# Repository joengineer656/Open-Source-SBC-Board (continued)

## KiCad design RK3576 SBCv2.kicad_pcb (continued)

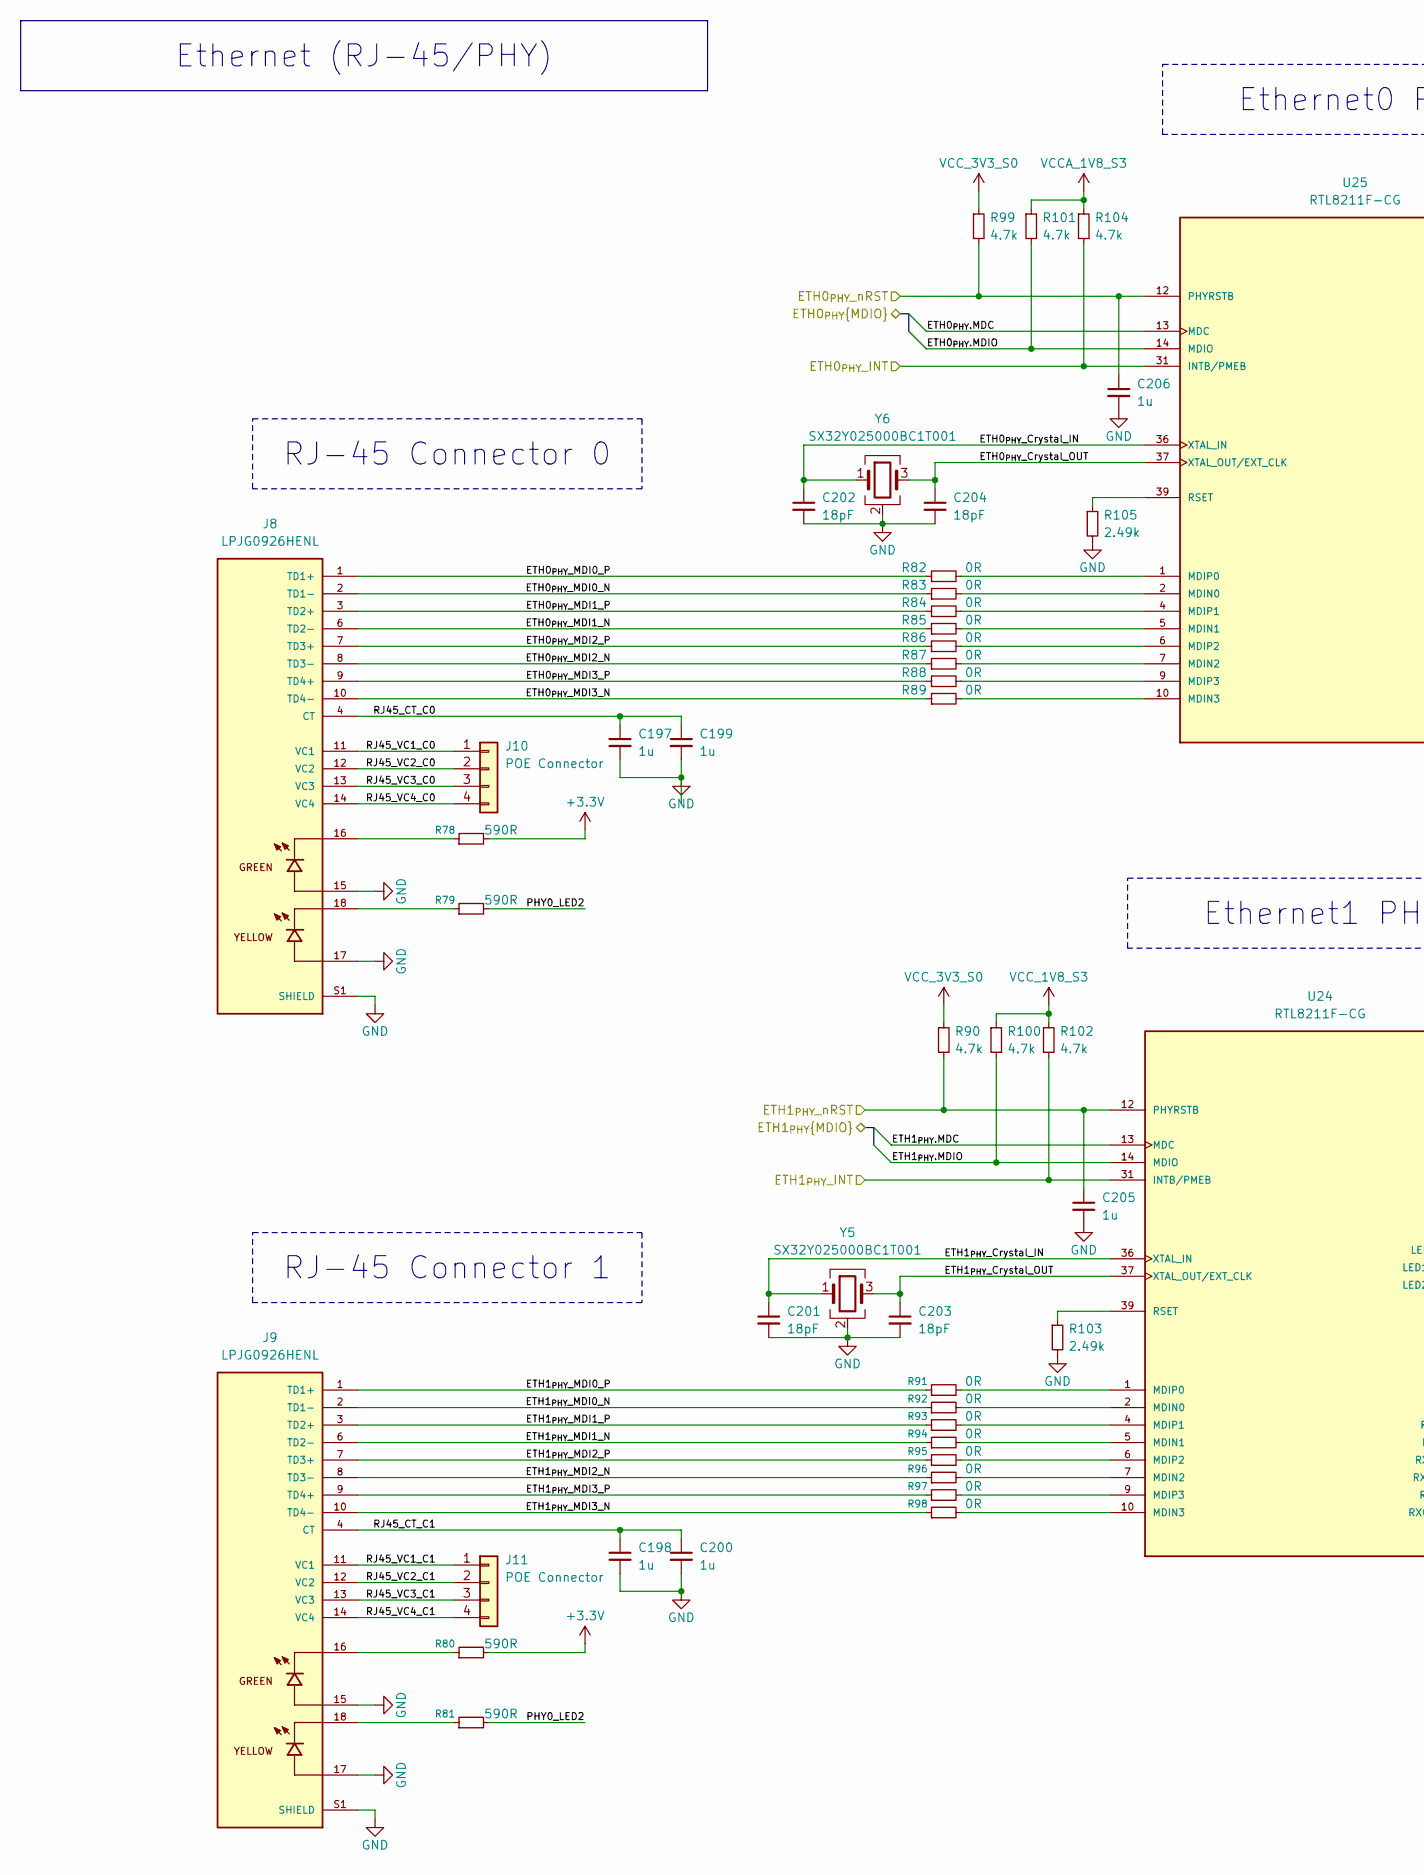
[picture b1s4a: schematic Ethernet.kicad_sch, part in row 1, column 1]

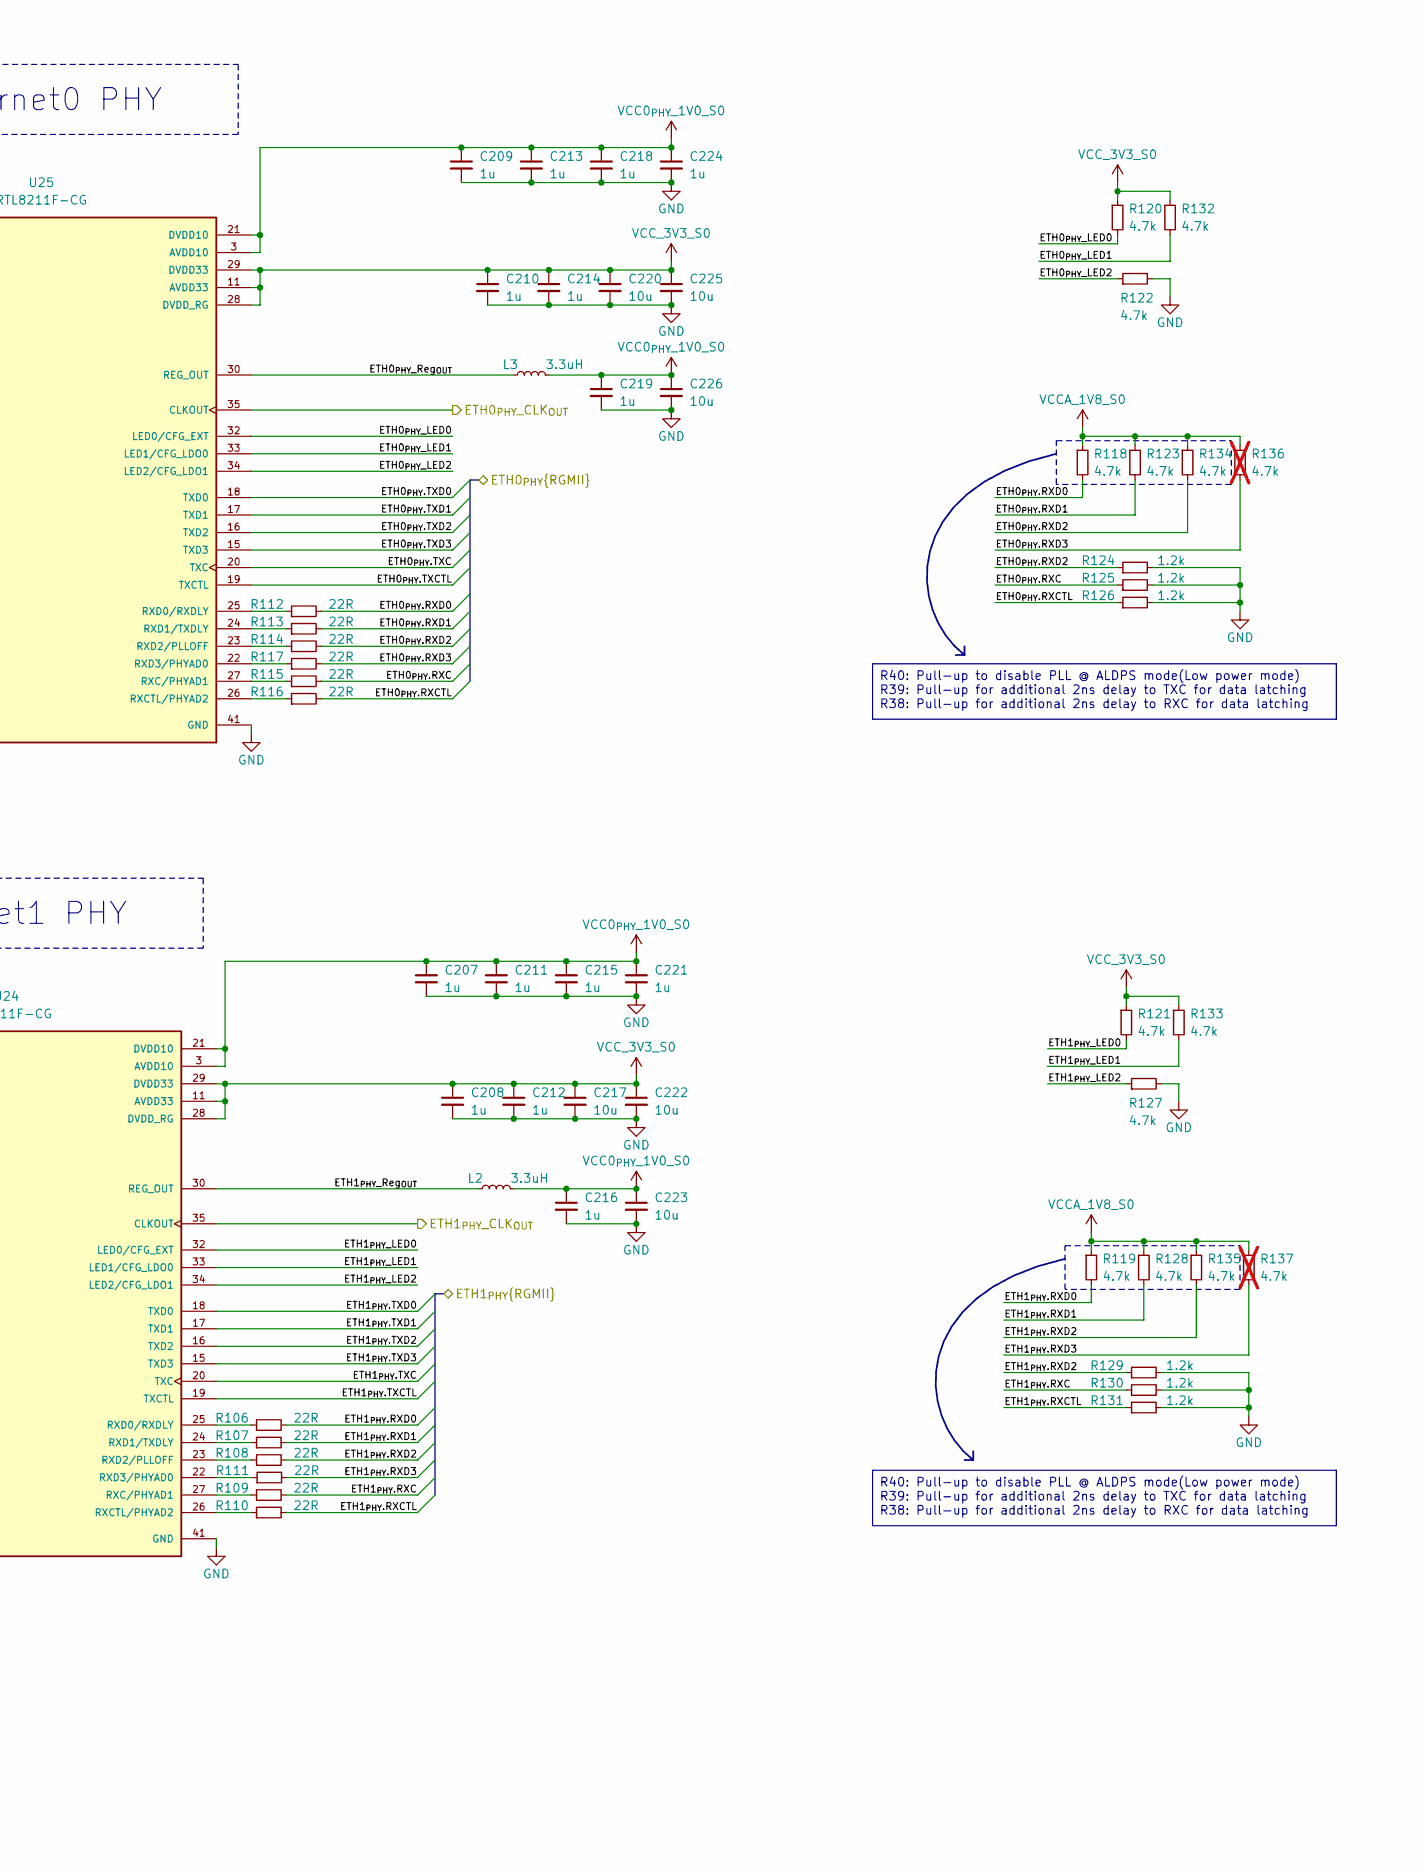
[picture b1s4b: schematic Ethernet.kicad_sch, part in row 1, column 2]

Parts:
C197, C198, C199, C200, C205, C206, C207, C208, C209, C210, C211, C212, C213, C214, C215, C216, C218, C219, C221, C224: 1u; C_0201_0603Metric_Pad0.64x0.40mm_HandSolder; Mouser Part CL03A105KP3NSNC; LCSC Part C5209398
C201, C202, C203, C204: 18pF; C_0402_1005Metric; Mouser Part 603-CC402FRNPO9BN180; LCSC Part C541431
C217, C220, C222, C223, C225, C226: 10u; C_0603_1608Metric; Mouser Part 187-CL10A106KP8NNNC; LCSC Part C19702
J8, J9: LPJG0926HENL; PARTREV A; LCSC Part C22457393
J10, J11: POE Connector; PinHeader_2x02_P2.54mm_Vertical; Mouser Part 200-TSW10207GDLL001; LCSC Part C66690
L2, L3: 3.3uH; L_Coilcraft_0805HQ_2012Metric; LCSC Part C2926398
R78, R79, R80, R81: 590R; R_0402_1005Metric; Mouser Part 603-RC0402FR-07590RL; LCSC Part C327335
R82, R83, R84, R85, R86, R87, R88, R89, R91, R92, R93, R94, R95, R96, R97, R98: 0R; R_0402_1005Metric; Mouser Part 603-RC0402FR-070RL; LCSC Part C106231
R90, R99, R100, R101, R102, R104, R118, R119, R120, R121, R122, R123, R127, R128, R132, R133, R134, R135: 4.7k; R_0402_1005Metric; Mouser Part 603-RC0402FR-074K7L; LCSC Part C105871
R103, R105: 2.49k; R_0402_1005Metric; Mouser Part 603-RC0402FR-074K7L; LCSC Part C105871
R106, R107, R108, R109, R110, R111, R112, R113, R114, R115, R116, R117: 22R; R_0402_1005Metric; Mouser Part 603-RC0402FR-070RL; LCSC Part C106231
R124, R125, R126, R129, R130, R131: 1.2k; R_0402_1005Metric; Mouser Part 603-RC0402FR-071K2L; LCSC Part C138040
R136, R137: 4.7k; R_0402_1005Metric; Mouser Part 603-RC0402FR-074K7L; LCSC Part C105871; not fitted
U24, U25: RTL8211F-CG; RTL8211F-CG_QFN-40-1EP_5x5mm_P0.4mm; PARTREV 1.4; LCSC Part C187932
Y5, Y6: SX32Y025000BC1T001; Crystal_SMD_3225-4Pin_3.2x2.5mm_HandSoldering; LCSC Part C20612981

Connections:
/Ethernet/ETH0_{PHY}.MDC: U25.13 (MDC); also elsewhere on the board
/Ethernet/ETH0_{PHY}.MDIO: R101.2, U25.14 (MDIO); also elsewhere on the board
/Ethernet/ETH0_{PHY}.RXC: R115.2, R125.1; also elsewhere on the board
/Ethernet/ETH0_{PHY}.RXCTL: R116.2, R126.1; also elsewhere on the board
/Ethernet/ETH0_{PHY}.RXD0: R112.2, R118.2; also elsewhere on the board
/Ethernet/ETH0_{PHY}.RXD1: R113.2, R123.2; also elsewhere on the board
/Ethernet/ETH0_{PHY}.RXD2: R114.2, R124.1, R134.2; also elsewhere on the board
/Ethernet/ETH0_{PHY}.RXD3: R117.2, R136.2; also elsewhere on the board
/Ethernet/ETH0_{PHY}.TXC: U25.20 (TXC); also elsewhere on the board
/Ethernet/ETH0_{PHY}.TXCTL: U25.19 (TXCTL); also elsewhere on the board
/Ethernet/ETH0_{PHY}.TXD0: U25.18 (TXD0); also elsewhere on the board
/Ethernet/ETH0_{PHY}.TXD1: U25.17 (TXD1); also elsewhere on the board
/Ethernet/ETH0_{PHY}.TXD2: U25.16 (TXD2); also elsewhere on the board
/Ethernet/ETH0_{PHY}.TXD3: U25.15 (TXD3); also elsewhere on the board
/Ethernet/ETH0_{PHY}_CLK_{OUT}: U25.35 (CLKOUT); also elsewhere on the board
/Ethernet/ETH0_{PHY}_Crystal_IN: C202.1, U25.36 (XTAL_IN), Y6.1
/Ethernet/ETH0_{PHY}_Crystal_OUT: C204.1, U25.37 (XTAL_OUT/EXT_CLK), Y6.3
/Ethernet/ETH0_{PHY}_INT: R104.2, U25.31 (INTB/PMEB); also elsewhere on the board
/Ethernet/ETH0_{PHY}_LED0: R120.2, U25.32 (LED0/CFG_EXT)
/Ethernet/ETH0_{PHY}_LED1: R132.2, U25.33 (LED1/CFG_LDO0)
/Ethernet/ETH0_{PHY}_LED2: R122.1, U25.34 (LED2/CFG_LDO1)
/Ethernet/ETH0_{PHY}_MDI0_N: J8.2 (TD1-), R83.1
/Ethernet/ETH0_{PHY}_MDI0_P: J8.1 (TD1+), R82.1
/Ethernet/ETH0_{PHY}_MDI1_N: J8.6 (TD2-), R85.1
/Ethernet/ETH0_{PHY}_MDI1_P: J8.3 (TD2+), R84.1
/Ethernet/ETH0_{PHY}_MDI2_N: J8.8 (TD3-), R87.1
/Ethernet/ETH0_{PHY}_MDI2_P: J8.7 (TD3+), R86.1
/Ethernet/ETH0_{PHY}_MDI3_N: J8.10 (TD4-), R89.1
/Ethernet/ETH0_{PHY}_MDI3_P: J8.9 (TD4+), R88.1
/Ethernet/ETH0_{PHY}_Reg_{OUT}: L3.1, U25.30 (REG_OUT)
/Ethernet/ETH0_{PHY}_nRST: C206.1, R99.2, U25.12 (PHYRSTB); also elsewhere on the board
/Ethernet/ETH1_{PHY}.MDC: U24.13 (MDC); also elsewhere on the board
/Ethernet/ETH1_{PHY}.MDIO: R100.2, U24.14 (MDIO); also elsewhere on the board
/Ethernet/ETH1_{PHY}.RXC: R109.2, R130.1; also elsewhere on the board
/Ethernet/ETH1_{PHY}.RXCTL: R110.2, R131.1; also elsewhere on the board
/Ethernet/ETH1_{PHY}.RXD0: R106.2, R119.2; also elsewhere on the board
/Ethernet/ETH1_{PHY}.RXD1: R107.2, R128.2; also elsewhere on the board
/Ethernet/ETH1_{PHY}.RXD2: R108.2, R129.1, R135.2; also elsewhere on the board
/Ethernet/ETH1_{PHY}.RXD3: R111.2, R137.2; also elsewhere on the board
/Ethernet/ETH1_{PHY}.TXC: U24.20 (TXC); also elsewhere on the board
/Ethernet/ETH1_{PHY}.TXCTL: U24.19 (TXCTL); also elsewhere on the board
/Ethernet/ETH1_{PHY}.TXD0: U24.18 (TXD0); also elsewhere on the board
/Ethernet/ETH1_{PHY}.TXD1: U24.17 (TXD1); also elsewhere on the board
/Ethernet/ETH1_{PHY}.TXD2: U24.16 (TXD2); also elsewhere on the board
/Ethernet/ETH1_{PHY}.TXD3: U24.15 (TXD3); also elsewhere on the board
/Ethernet/ETH1_{PHY}_CLK_{OUT}: U24.35 (CLKOUT); also elsewhere on the board
/Ethernet/ETH1_{PHY}_Crystal_IN: C201.1, U24.36 (XTAL_IN), Y5.1
/Ethernet/ETH1_{PHY}_Crystal_OUT: C203.1, U24.37 (XTAL_OUT/EXT_CLK), Y5.3
/Ethernet/ETH1_{PHY}_INT: R102.2, U24.31 (INTB/PMEB); also elsewhere on the board
/Ethernet/ETH1_{PHY}_LED0: R121.2, U24.32 (LED0/CFG_EXT)
/Ethernet/ETH1_{PHY}_LED1: R133.2, U24.33 (LED1/CFG_LDO0)
/Ethernet/ETH1_{PHY}_LED2: R127.1, U24.34 (LED2/CFG_LDO1)
/Ethernet/ETH1_{PHY}_MDI0_N: J9.2 (TD1-), R92.1
/Ethernet/ETH1_{PHY}_MDI0_P: J9.1 (TD1+), R91.1
/Ethernet/ETH1_{PHY}_MDI1_N: J9.6 (TD2-), R94.1
/Ethernet/ETH1_{PHY}_MDI1_P: J9.3 (TD2+), R93.1
/Ethernet/ETH1_{PHY}_MDI2_N: J9.8 (TD3-), R96.1
/Ethernet/ETH1_{PHY}_MDI2_P: J9.7 (TD3+), R95.1
/Ethernet/ETH1_{PHY}_MDI3_N: J9.10 (TD4-), R98.1
/Ethernet/ETH1_{PHY}_MDI3_P: J9.9 (TD4+), R97.1
/Ethernet/ETH1_{PHY}_Reg_{OUT}: L2.1, U24.30 (REG_OUT)
/Ethernet/ETH1_{PHY}_nRST: C205.1, R90.2, U24.12 (PHYRSTB); also elsewhere on the board
/Ethernet/PHY0_LED2: R79.2, R81.2
/Ethernet/RJ45_CT_C0: C197.1, C199.1, J8.4 (CT), J8.5 (CT)
/Ethernet/RJ45_CT_C1: C198.1, C200.1, J9.4 (CT), J9.5 (CT)
/Ethernet/RJ45_VC1_C0: J8.11 (VC1), J10.1
/Ethernet/RJ45_VC1_C1: J9.11 (VC1), J11.1
/Ethernet/RJ45_VC2_C0: J8.12 (VC2), J10.2
/Ethernet/RJ45_VC2_C1: J9.12 (VC2), J11.2
/Ethernet/RJ45_VC3_C0: J8.13 (VC3), J10.3
/Ethernet/RJ45_VC3_C1: J9.13 (VC3), J11.3
/Ethernet/RJ45_VC4_C0: J8.14 (VC4), J10.4
/Ethernet/RJ45_VC4_C1: J9.14 (VC4), J11.4
unnamed: J8.16, R78.1
unnamed: J8.18, R79.1
unnamed: J9.16, R80.1
unnamed: J9.18, R81.1
unnamed: R92.2, U24.2 (MDIN0)
unnamed: R94.2, U24.5 (MDIN1)
unnamed: R96.2, U24.7 (MDIN2)
unnamed: R98.2, U24.10 (MDIN3)
unnamed: R91.2, U24.1 (MDIP0)
unnamed: R93.2, U24.4 (MDIP1)
unnamed: R95.2, U24.6 (MDIP2)
unnamed: R97.2, U24.9 (MDIP3)
unnamed: R103.1, U24.39 (RSET)
unnamed: R110.1, U24.26 (RXCTL/PHYAD2)
unnamed: R109.1, U24.27 (RXC/PHYAD1)
unnamed: R106.1, U24.25 (RXD0/RXDLY)
unnamed: R107.1, U24.24 (RXD1/TXDLY)
unnamed: R108.1, U24.23 (RXD2/PLLOFF)
unnamed: R111.1, U24.22 (RXD3/PHYAD0)
unnamed: R83.2, U25.2 (MDIN0)
unnamed: R85.2, U25.5 (MDIN1)
unnamed: R87.2, U25.7 (MDIN2)
unnamed: R89.2, U25.10 (MDIN3)
unnamed: R82.2, U25.1 (MDIP0)
unnamed: R84.2, U25.4 (MDIP1)
unnamed: R86.2, U25.6 (MDIP2)
unnamed: R88.2, U25.9 (MDIP3)
unnamed: R105.1, U25.39 (RSET)
unnamed: R116.1, U25.26 (RXCTL/PHYAD2)
unnamed: R115.1, U25.27 (RXC/PHYAD1)
unnamed: R112.1, U25.25 (RXD0/RXDLY)
unnamed: R113.1, U25.24 (RXD1/TXDLY)
unnamed: R114.1, U25.23 (RXD2/PLLOFF)
unnamed: R117.1, U25.22 (RXD3/PHYAD0)
VCC0_{PHY}_1V0_S0: C207.1, C209.1, C211.1, C213.1, C215.1, C216.1, C218.1, C219.1, C221.1, C223.1, C224.1, C226.1, L2.2, L3.2, U24.3 (AVDD10), U24.8 (AVDD10), U24.21 (DVDD10), U24.38 (AVDD10), U25.3 (AVDD10), U25.8 (AVDD10), U25.21 (DVDD10), U25.38 (AVDD10)
VCCA_1V8_S3: R101.1, R104.1; also elsewhere on the board

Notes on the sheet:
R40: Pull-up to disable PLL @ ALDPS mode(Low power mode) R39: Pull-up for additional 2ns delay to TXC for data latching R38: Pull-up for additional 2ns delay to RXC for data latching
RJ-45 Connector 1
Ethernet (RJ-45/PHY)
Ethernet1 PHY
Ethernet0 PHY
RJ-45 Connector 0

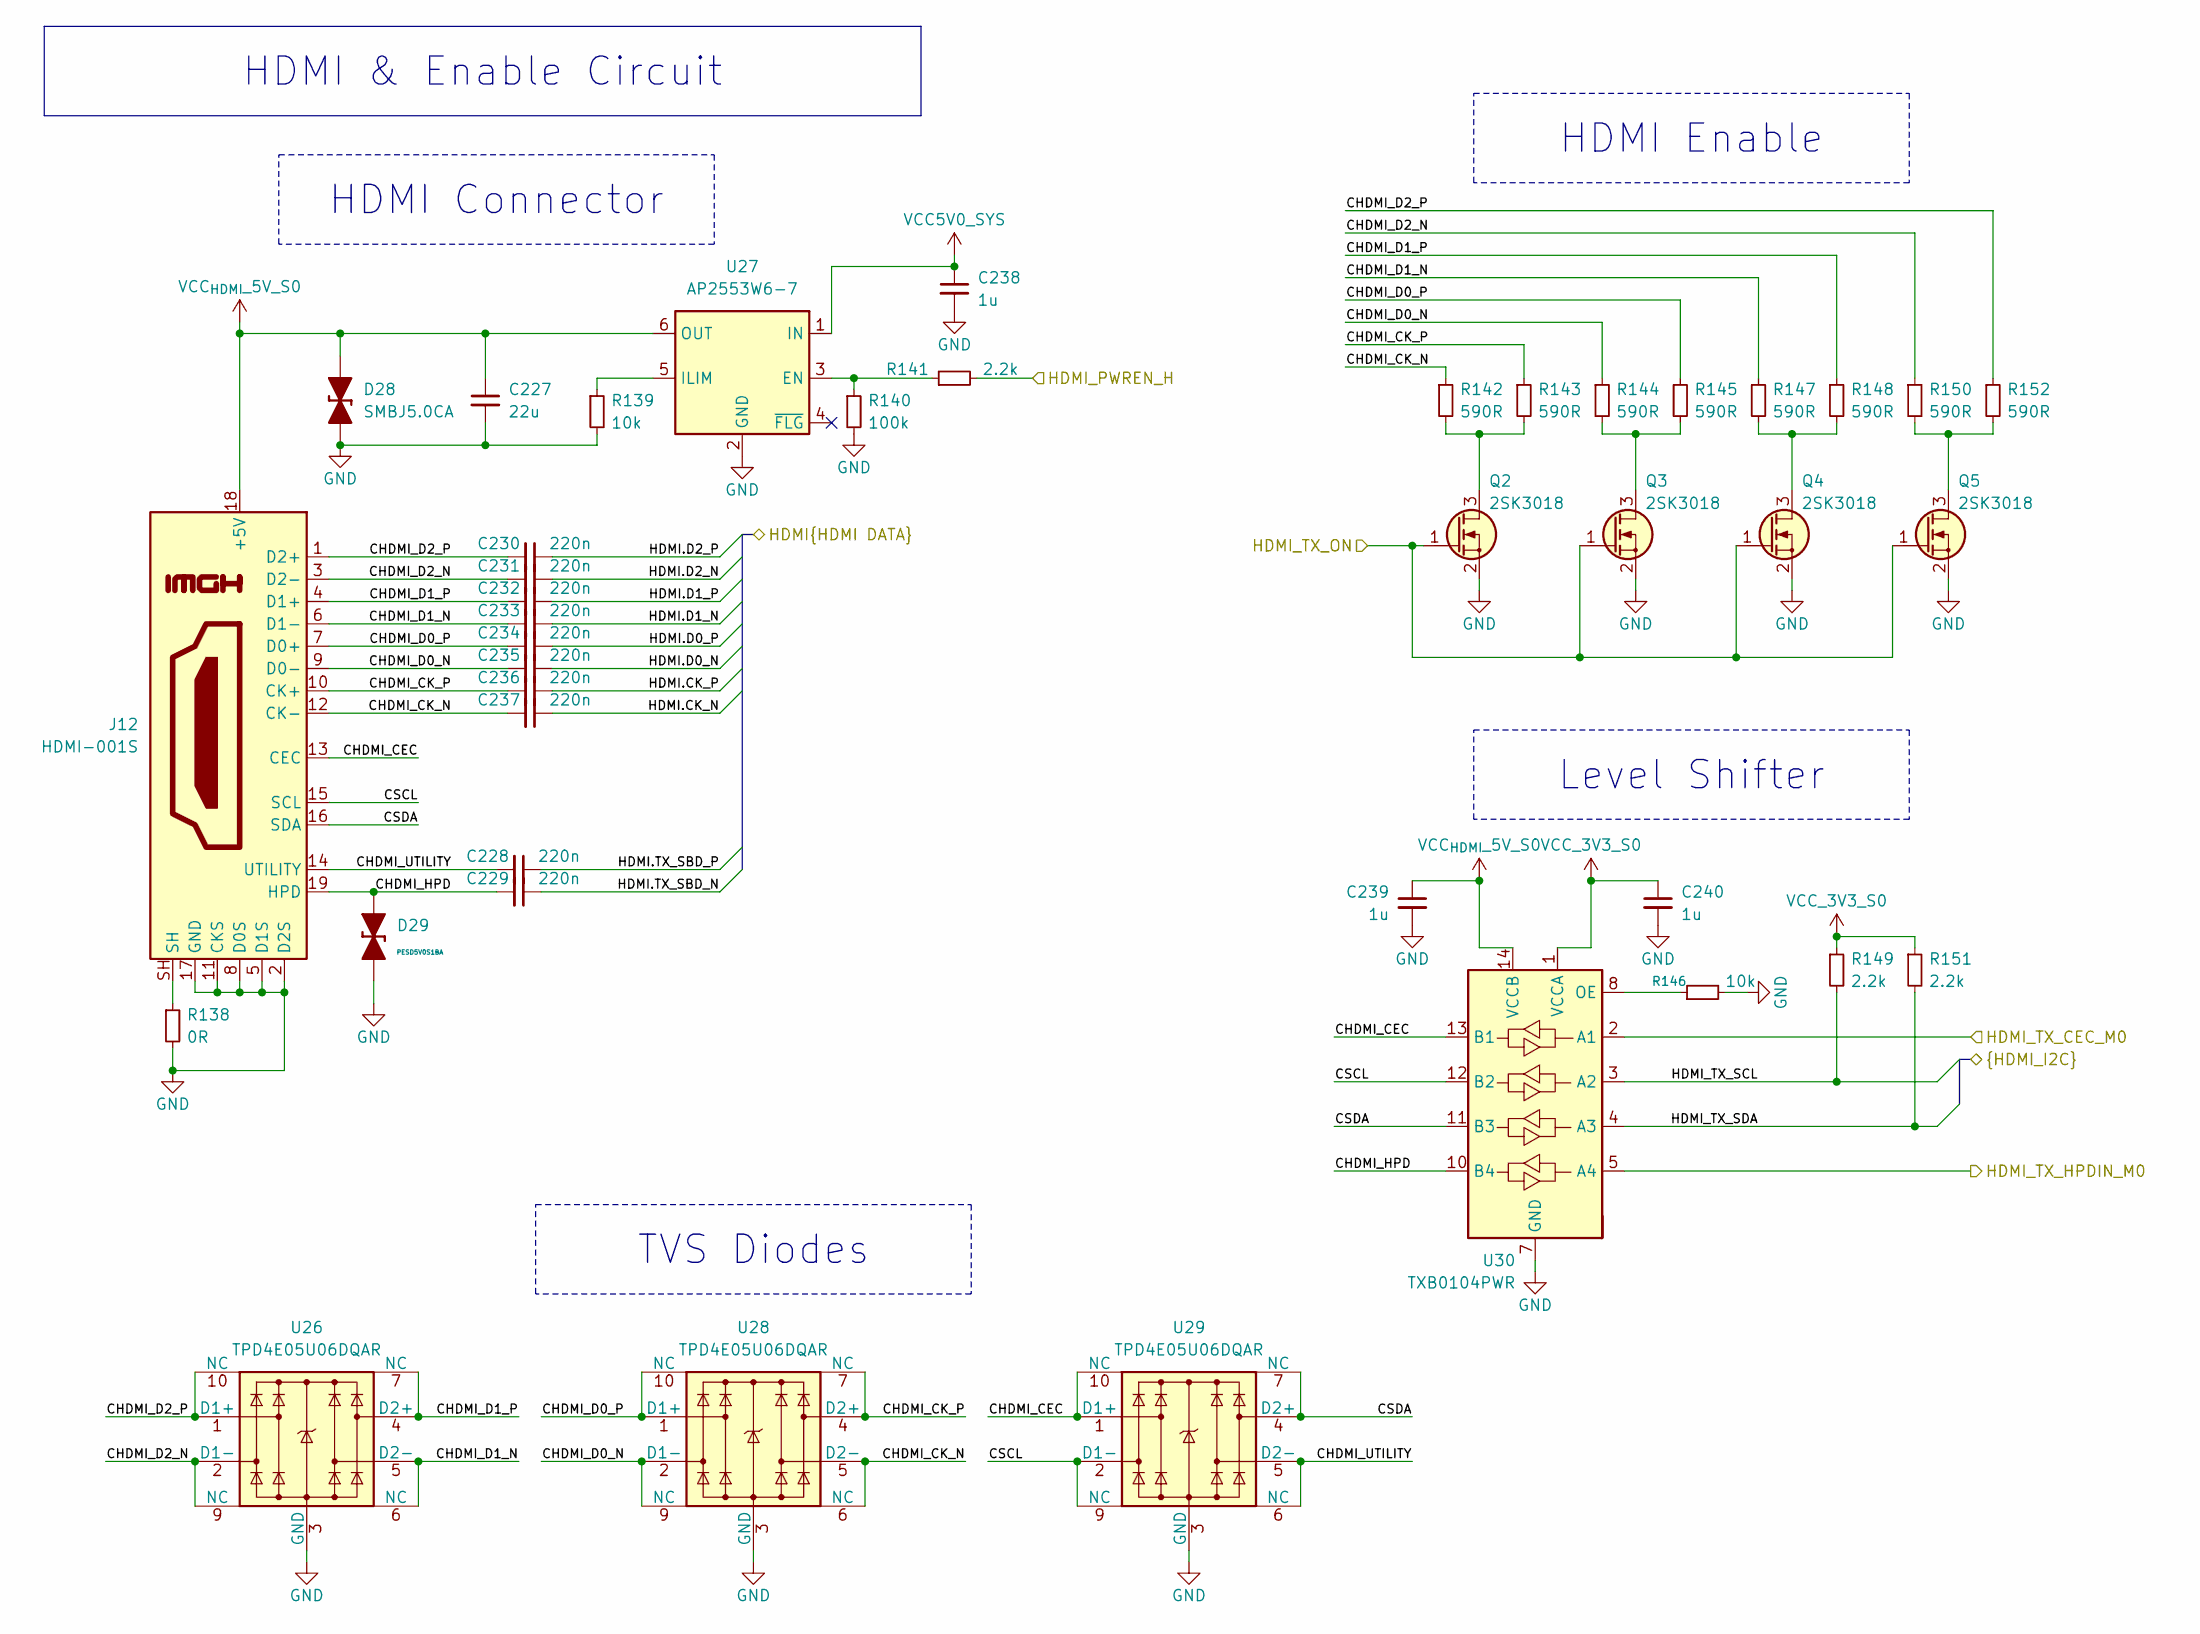
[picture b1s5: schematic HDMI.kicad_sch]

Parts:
C227: 22u; C_0603_1608Metric; Mouser Part CL10A226MP8NUNE; LCSC Part C86295
C228, C229, C230, C231, C232, C233, C234, C235, C236, C237: 220n; C_0201_0603Metric_Pad0.64x0.40mm_HandSolder; Mouser Part 603-CC0201KRX56BB224; LCSC Part C326658
C238, C239, C240: 1u; C_0201_0603Metric_Pad0.64x0.40mm_HandSolder; Mouser Part CL03A105KP3NSNC; LCSC Part C5209398
D28: SMBJ5.0CA; D_SMB_TVS; Mouser Part 581-SMBJ5.0CA; LCSC Part C113975
D29: PESD5V0S1BA; D_SOD-323_TVS; Mouser Part 771-PESD5V0S1BA-T/R; LCSC Part C5158048
J12: HDMI-001S; HDMI_A_Amphenol_10029449-x01xLF_Horizontal; LCSC Part C720616
Q2, Q3, Q4, Q5: 2SK3018; SOT-323_SC-70; LCSC Part C20069148
R138: 0R; R_0402_1005Metric; Mouser Part 603-RC0402FR-070RL; LCSC Part C106231
R139, R146: 10k; R_0402_1005Metric; Mouser Part 603-RC0402FR-0710KL; LCSC Part C60490
R140: 100k; R_0402_1005Metric; Mouser Part 603-RC0402FR-0710KL; LCSC Part C60490
R141, R149, R151: 2.2k; R_0402_1005Metric; Mouser Part 603-RC0402FR-072K2L; LCSC Part C114762
R142, R143, R144, R145, R147, R148, R150, R152: 590R; R_0402_1005Metric; Mouser Part 603-RC0402FR-07590RL; LCSC Part C327335
U26, U28, U29: TPD4E05U06DQAR; USON-10_2.5x1.0mm_P0.5mm; Mouser Part 595-TPD4E05U06DQAR; LCSC Part C138714
U27: AP2553W6-7; SOT-23-6_Handsoldering; Mouser Part 621-AP2553W6-7; LCSC Part C212302
U30: TXB0104PWR; TSSOP-14_4.4x5mm_P0.65mm; Mouser Part 595-TXB0104PWR; LCSC Part C60708

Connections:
/HDMI/CHDMI_CEC: J12.13 (CEC), U29.1 (D1+), U29.10 (NC), U30.13 (B1)
/HDMI/CHDMI_CK_N: C237.2, J12.12 (CK-), R142.1, U28.5 (D2-), U28.6 (NC)
/HDMI/CHDMI_CK_P: C236.2, J12.10 (CK+), R143.1, U28.4 (D2+), U28.7 (NC)
/HDMI/CHDMI_D0_N: C235.2, J12.9 (D0-), R144.1, U28.2 (D1-), U28.9 (NC)
/HDMI/CHDMI_D0_P: C234.2, J12.7 (D0+), R145.1, U28.1 (D1+), U28.10 (NC)
/HDMI/CHDMI_D1_N: C233.2, J12.6 (D1-), R147.1, U26.5 (D2-), U26.6 (NC)
/HDMI/CHDMI_D1_P: C232.2, J12.4 (D1+), R148.1, U26.4 (D2+), U26.7 (NC)
/HDMI/CHDMI_D2_N: C231.2, J12.3 (D2-), R150.1, U26.2 (D1-), U26.9 (NC)
/HDMI/CHDMI_D2_P: C230.2, J12.1 (D2+), R152.1, U26.1 (D1+), U26.10 (NC)
/HDMI/CHDMI_HPD: C229.2, D29.2 (A), J12.19 (HPD), U30.10 (B4)
/HDMI/CHDMI_UTILITY: C228.2, J12.14 (UTILITY), U29.5 (D2-), U29.6 (NC)
/HDMI/CSCL: J12.15 (SCL), U29.2 (D1-), U29.9 (NC), U30.12 (B2)
/HDMI/CSDA: J12.16 (SDA), U29.4 (D2+), U29.7 (NC), U30.11 (B3)
/HDMI/HDMI.CK_N: C237.1
/HDMI/HDMI.CK_P: C236.1
/HDMI/HDMI.D0_N: C235.1
/HDMI/HDMI.D0_P: C234.1
/HDMI/HDMI.D1_N: C233.1
/HDMI/HDMI.D1_P: C232.1
/HDMI/HDMI.D2_N: C231.1
/HDMI/HDMI.D2_P: C230.1
/HDMI/HDMI.TX_SBD_N: C229.1
/HDMI/HDMI.TX_SBD_P: C228.1
/HDMI/HDMI_PWREN_H: R141.2; also elsewhere on the board
/HDMI/HDMI_TX_CEC_M0: U30.2 (A1); also elsewhere on the board
/HDMI/HDMI_TX_HPDIN_M0: U30.5 (A4); also elsewhere on the board
/HDMI/HDMI_TX_ON: Q2.1 (G), Q3.1 (G), Q4.1 (G), Q5.1 (G); also elsewhere on the board
/HDMI/HDMI_TX_SCL: R149.2, U30.3 (A2); also elsewhere on the board
/HDMI/HDMI_TX_SDA: R151.2, U30.4 (A3); also elsewhere on the board
unnamed: J12.SH, R138.1
unnamed: Q2.3 (D), R142.2, R143.2
unnamed: Q3.3 (D), R144.2, R145.2
unnamed: Q4.3 (D), R147.2, R148.2
unnamed: Q5.3 (D), R150.2, R152.2
unnamed: R140.1, R141.1, U27.3 (EN)
unnamed: R139.1, U27.5 (ILIM)
unnamed: R146.1, U30.8 (OE)
VCC_{HDMI}_5V_S0: C227.1, C239.1, D28.2 (A), J12.18 (+5V), U27.6 (OUT), U30.14 (VCCB)

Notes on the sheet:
TVS Diodes
HDMI Connector
Level Shifter
HDMI & Enable Circuit
HDMI Enable

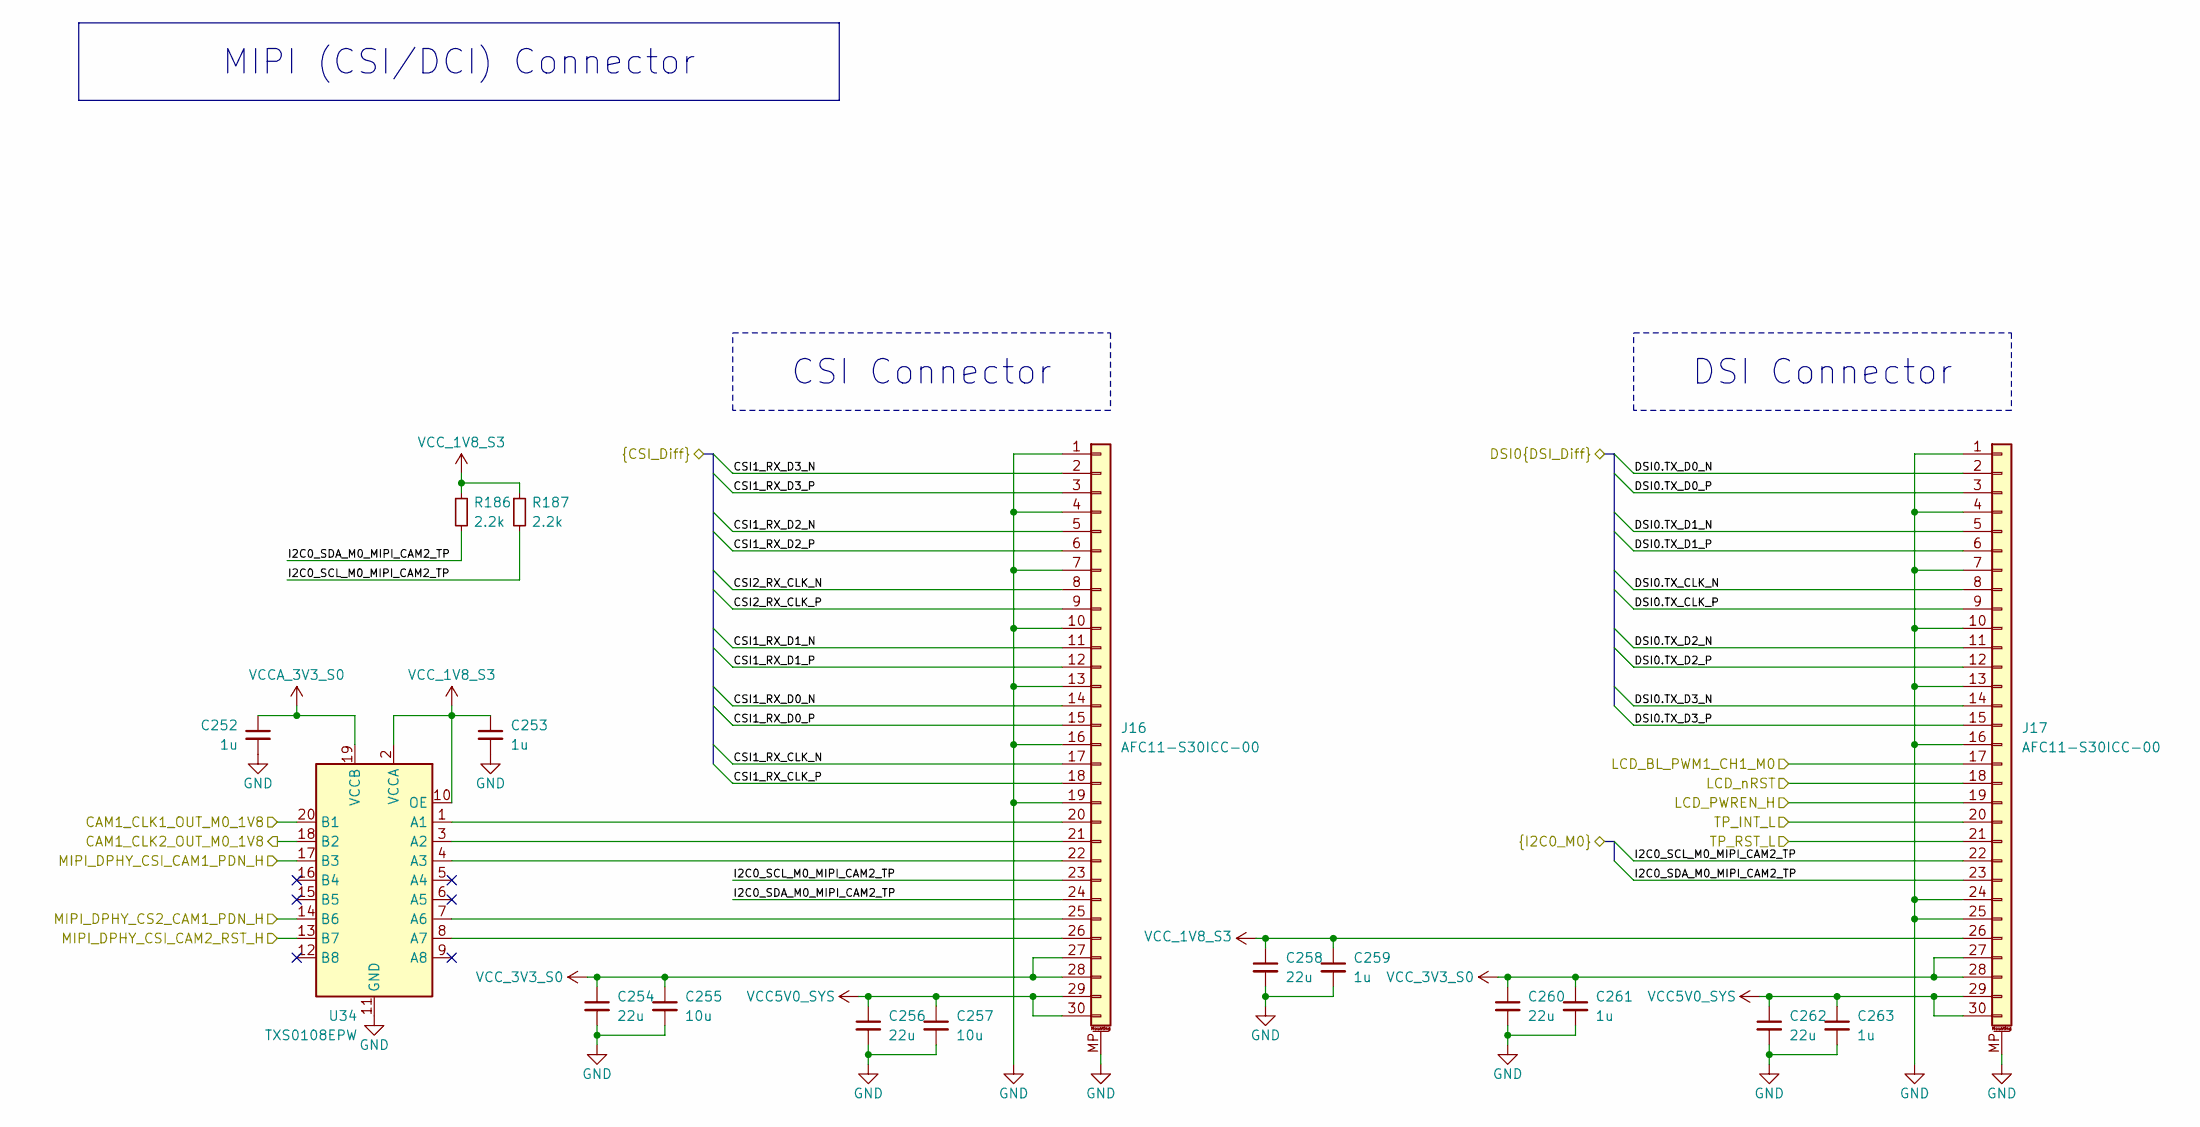
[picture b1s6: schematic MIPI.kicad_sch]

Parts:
C252, C253, C259, C261, C263: 1u; C_0201_0603Metric_Pad0.64x0.40mm_HandSolder; Mouser Part CL03A105KP3NSNC; LCSC Part C5209398
C254, C256, C258, C260, C262: 22u; C_0603_1608Metric; Mouser Part CL10A226MP8NUNE; LCSC Part C86295
C255, C257: 10u; C_0603_1608Metric; Mouser Part 187-CL10A106KP8NNNC; LCSC Part C19702
J16, J17: AFC11-S30ICC-00; FPC-SMD_30P-L20.5-W2.0-P0.50; Mouser Part 38-52559-3052; LCSC Part C11078
R186, R187: 2.2k; R_0402_1005Metric; Mouser Part 603-RC0402FR-072K2L; LCSC Part C114762
U34: TXS0108EPW; TXS0108ERGYR_VQFN-20-EP_C90706; Mouser Part TXS0108ERGYR; LCSC Part C90706

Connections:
/MIPI/CAM1_CLK1_OUT_M0_1V8: U34.20 (B1); also elsewhere on the board
/MIPI/CAM1_CLK2_OUT_M0_1V8: U34.18 (B2); also elsewhere on the board
/MIPI/CSI1_RX_CLK_N: J16.17
/MIPI/CSI1_RX_D0_N: J16.14
/MIPI/CSI1_RX_D1_P: J16.12
/MIPI/DSI0.TX_D2_P: J17.12; also elsewhere on the board
/MIPI/LCD_BL_PWM1_CH1_M0: J17.17; also elsewhere on the board
/MIPI/LCD_PWREN_H: J17.19; also elsewhere on the board
/MIPI/MIPI_DPHY_CS2_CAM1_PDN_H: U34.14 (B6); also elsewhere on the board
/MIPI/MIPI_DPHY_CSI_CAM1_PDN_H: U34.17 (B3); also elsewhere on the board
/MIPI/MIPI_DPHY_CSI_CAM2_RST_H: U34.13 (B7); also elsewhere on the board
unnamed: J16.22, U34.4 (A3)
unnamed: J16.25, U34.7 (A6)

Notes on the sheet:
DSI Connector
CSI Connector
MIPI (CSI/DCI) Connector

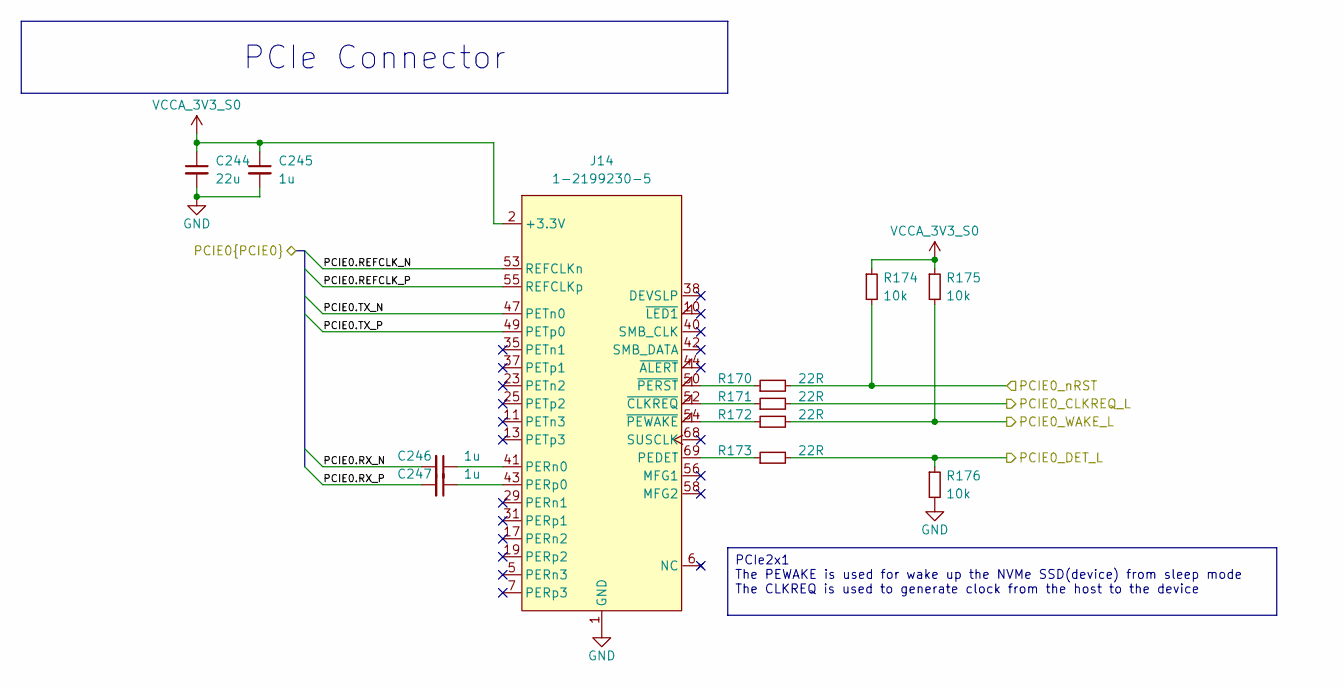
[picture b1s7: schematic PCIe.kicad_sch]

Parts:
C244: 22u; C_0603_1608Metric; Mouser Part CL10A226MP8NUNE; LCSC Part C86295
C245, C246, C247: 1u; C_0201_0603Metric_Pad0.64x0.40mm_HandSolder; Mouser Part CL03A105KP3NSNC; LCSC Part C5209398
J14: 1-2199230-5; PCIE-SMD_75P-P0.50_1-2199230-5; MPN 1-2199230-5; LCSC Part C590854
R170, R171, R172, R173: 22R; R_0402_1005Metric; Mouser Part 603-RC0402FR-070RL; LCSC Part C106231
R174, R175, R176: 10k; R_0402_1005Metric; Mouser Part 603-RC0402FR-0710KL; LCSC Part C60490

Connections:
/PCIe/PCIE0.REFCLK_N: J14.53 (REFCLKn); also elsewhere on the board
/PCIe/PCIE0.REFCLK_P: J14.55 (REFCLKp); also elsewhere on the board
/PCIe/PCIE0.RX_N: C246.2; also elsewhere on the board
/PCIe/PCIE0.RX_P: C247.2; also elsewhere on the board
/PCIe/PCIE0.TX_N: J14.47 (PETn0); also elsewhere on the board
/PCIe/PCIE0.TX_P: J14.49 (PETp0); also elsewhere on the board
/PCIe/PCIE0_CLKREQ_L: R171.2; also elsewhere on the board
/PCIe/PCIE0_DET_L: R173.2, R176.1; also elsewhere on the board
/PCIe/PCIE0_WAKE_L: R172.2, R175.2; also elsewhere on the board
/PCIe/PCIE0_nRST: R170.2, R174.2; also elsewhere on the board
unnamed: J14.69 (PEDET), R173.1
unnamed: C246.1, J14.41 (PERn0)
unnamed: C247.1, J14.43 (PERp0)
unnamed: J14.52 (~CLKREQ), R171.1
unnamed: J14.50 (~PERST), R170.1
unnamed: J14.54 (~PEWAKE), R172.1

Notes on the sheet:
PCIe2x1 The PEWAKE is used for wake up the NVMe SSD(device) from sleep mode The CLKREQ is used to generate clock from the host to the device
PCIe Connector
